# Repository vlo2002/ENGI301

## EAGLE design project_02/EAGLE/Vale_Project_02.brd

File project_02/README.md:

<h1> Taylor Swift vs. Shakespeare Trivia Game PCB Design </h1>
<h2> Project Overview </h2>
Ever since I was young, I've been an avid listener of Taylor Swift. My favorite thing about her songs were her lyrics, and as I've grown up through my teen years, I've watched her lyrics develop with her career. Some of her later work has very sophisticated lyricism drawing from famous poetry and literature. I wanted to make a game that was both engaging and challenging, and made the player acknowledge some of their inherent preconception of Taylor Swift lyrics. For this project, I created a portable trivia game with two buttons and an SPI screen, coded to boot on power and run for 60 seconds as the user answers as many questions as they can. Then, the game outputs a score on the screen, and you can repeat this cycle. The block diagrams and hardware setup for the build device are documented on my Hackster.io page: https://www.hackster.io/511943/who-said-it-taylor-swift-vs-shakespeare-trivia-fd3cca. 

<h2> Navigating the Project 2 Repository </h2>
All of the documentatio for the PCB design can be found in the Project 2 folders. In the general project 2 folder, you can find the OCB BOM, top and bottom assembly pdfs, and a pdf of the device schematic frmo EAGLE. The contents of each folder are outlined below:
1. /docs folder contains the mechanical and system block diagrams for the device, including the mechanical layout of components on the PCB. It also contains the top and bottom views of the PCB assembly.
2. /EAGLE folder contains the .brd, .sch, and .lbr files for the PCB
3. /CAMOutputs folder contains the MFG files, including assembly files, drill files, and gerber files
4. /Macrofab folder contines the Macrofab BOM, a .txt with my account info for lookup, and a pdf of a representative quote approximation for the manufacturing of one (1) unit of my PCB. I also got quotes for 10, 100, and 1000 units. With a 17-day lead time, 1 board costed $1,004.37, 10 boards costed $1,374.15, 100 boards costed $3,246.26, and 1000 boards costed $16,609.49.

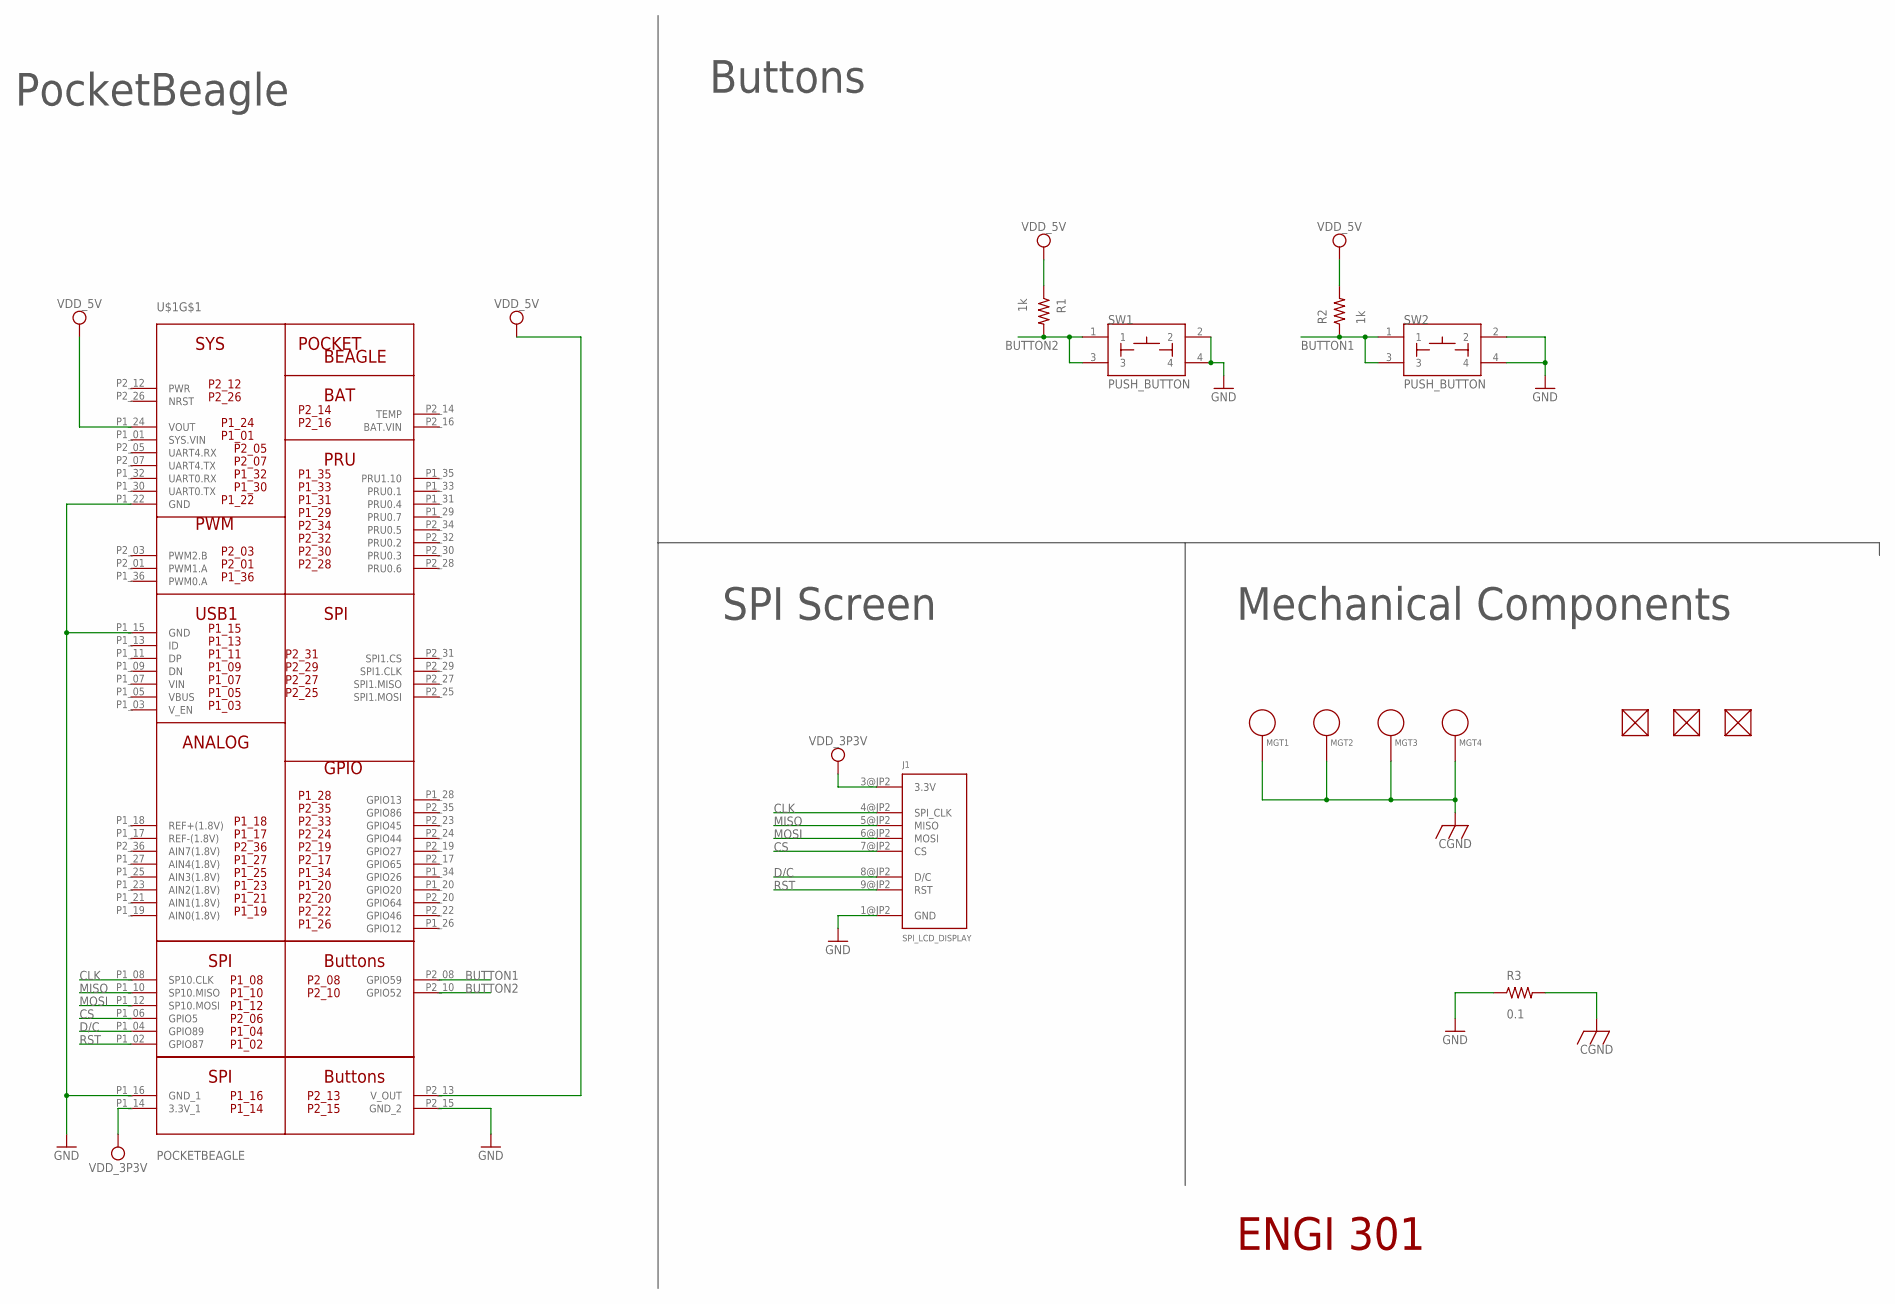
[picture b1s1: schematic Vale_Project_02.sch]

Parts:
FUD1, FUD2, FUD3: FIDUCIAL; FIDUCIAL_40MIL
J1: SPI_LCD_DISPLAY
MGT1, MGT2, MGT3, MGT4: MOUNTING_HOLE
R1, R2: 1k; R1206
R3: 0.1; R0805
SW1, SW2: PUSH_BUTTON; BUTTON_12.5MM
U$1: POCKETBEAGLE

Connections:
BUTTON1: R2.1, SW2.1, SW2.3, U$1.P2_08 (GPIO59)
BUTTON2: R1.2, SW1.1, SW1.3, U$1.P2_10 (GPIO52)
CGND: MGT1.P$1, MGT2.P$1, MGT3.P$1, MGT4.P$1, R3.2
CLK: J1.4@JP2 (SPI_CLK), U$1.P1_08 (SP10.CLK)
CS: J1.7@JP2 (CS), U$1.P1_06 (GPIO5)
D/C: J1.8@JP2 (D/C), U$1.P1_04 (GPIO89)
GND: J1.1@JP2 (GND), R3.1, SW1.2, SW1.4, SW2.2, SW2.4, U$1.P1_15 (GND), U$1.P1_16 (GND_1), U$1.P1_22 (GND), U$1.P2_15 (GND_2)
MISO: J1.5@JP2 (MISO), U$1.P1_10 (SP10.MISO)
MOSI: J1.6@JP2 (MOSI), U$1.P1_12 (SP10.MOSI)
RST: J1.9@JP2 (RST), U$1.P1_02 (GPIO87)
VDD_3P3V: J1.3@JP2 (3.3V), U$1.P1_14 (3.3V_1)
VDD_5V: R1.1, R2.2, U$1.P1_24 (VOUT), U$1.P2_13 (V_OUT)

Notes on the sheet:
Buttons
PocketBeagle
SPI Screen
ENGI 301
Mechanical Components

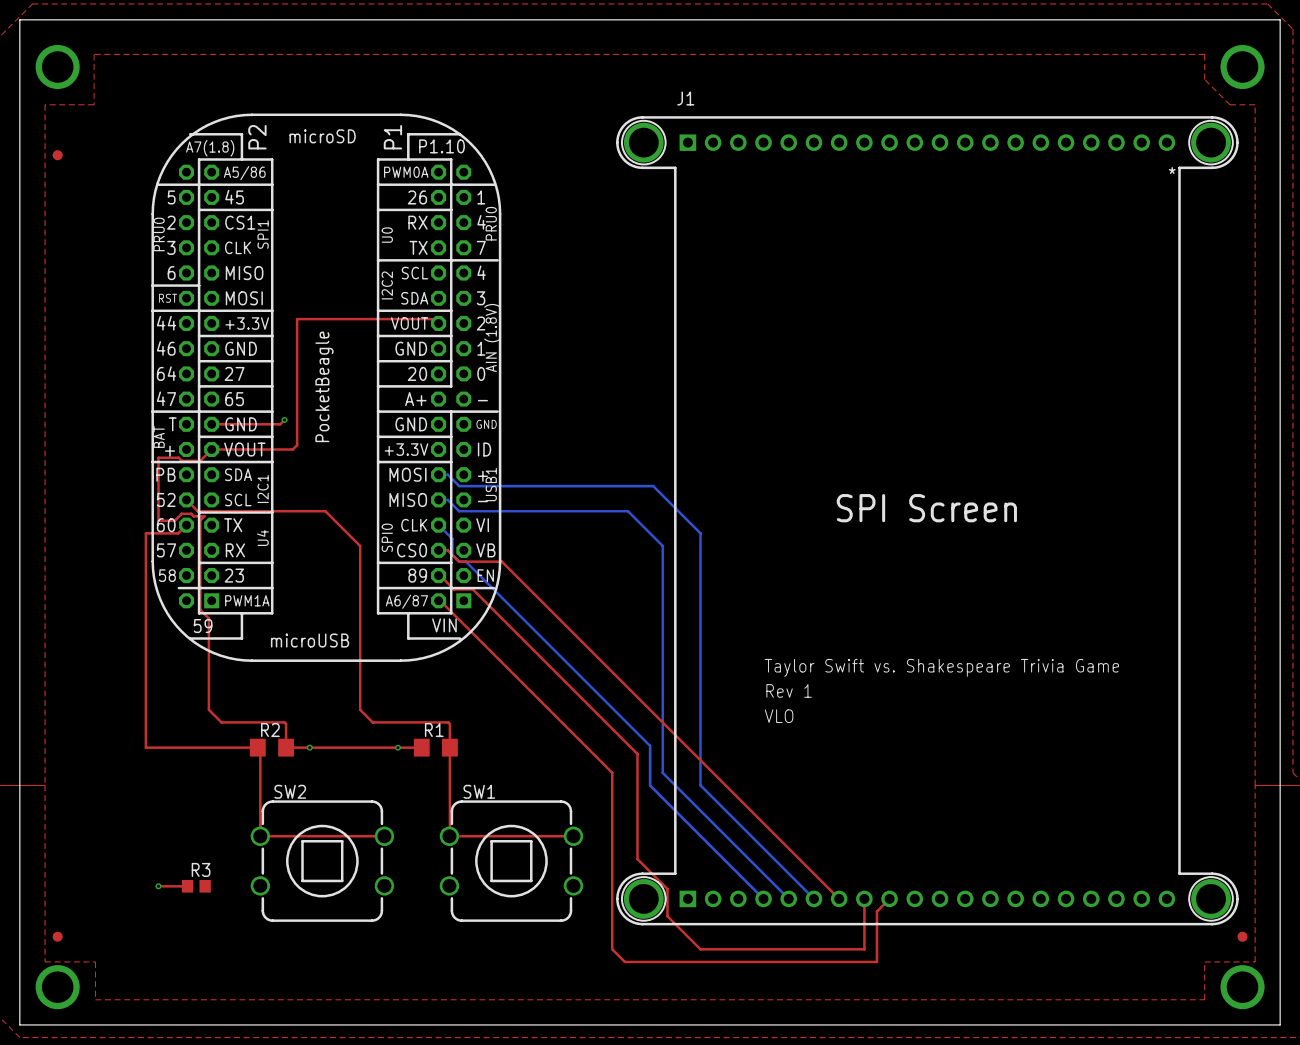
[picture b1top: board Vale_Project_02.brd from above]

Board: 4 copper layers, 127.0 x 101.3 mm, 14 parts (0 on the bottom side), 12 nets.

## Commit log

2023-09-28 Simple Calculator Functions, HW 4 Problem 1
2023-09-28 Blinking LED Assignment HW 4 Problem 2
2023-09-28 HW 4 Problem 3 button
2023-11-07 Uploading Project 01 ENGI 301 Folder
2023-12-12 Create System Block Diagram
2023-12-12 Create Mechanical Block Diagram Project_02.png.
